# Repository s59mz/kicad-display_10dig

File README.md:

# kicad-display_10dig
A simple 10-digit 7-segment display with keyboard and PMOD interface

Schematic:
[display_10dig.pdf](display_10dig.pdf)

BOM:
[display_10dig.csv](display_10dig.csv)

Gerbers:
[gerbers.zip](https://github.com/s59mz/kicad-display_10dig/raw/main/gerbers.zip)
~

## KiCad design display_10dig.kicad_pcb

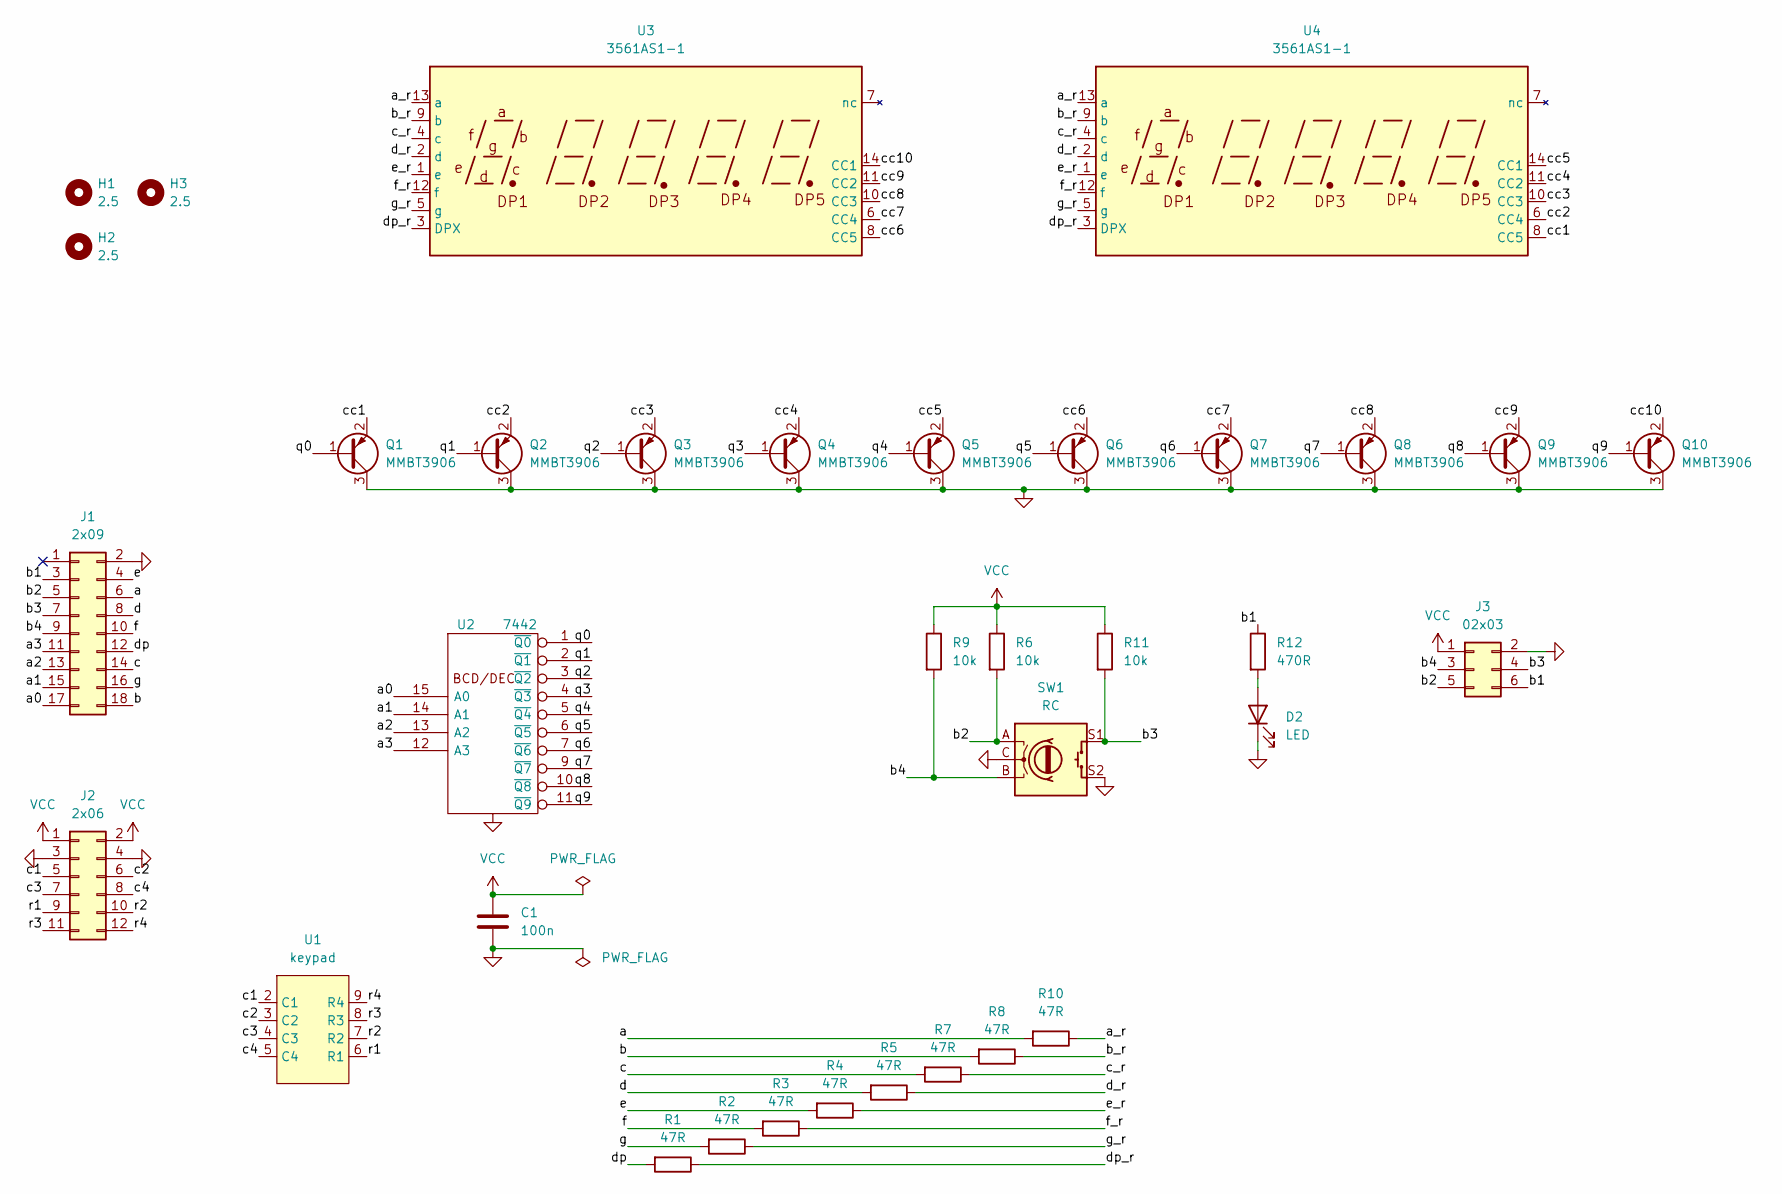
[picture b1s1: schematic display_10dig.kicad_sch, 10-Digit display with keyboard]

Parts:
C1: 100n; C_0603_1608Metric_Pad1.08x0.95mm_HandSolder
D2: LED; LED_D3.0mm
H1, H2, H3: 2.5; MountingHole_2.7mm_M2.5
J1: 2x09; PinHeader_2x09_P2.54mm_Horizontal
J2: 2x06; PinHeader_2x06_P2.54mm_Horizontal
J3: 02x03; PinHeader_2x03_P2.54mm_Vertical
Q1, Q2, Q3, Q4, Q5, Q6, Q7, Q8, Q9, Q10: MMBT3906; SOT-23
R1, R2, R3, R4, R5, R7, R8, R10: 47R; R_0603_1608Metric_Pad0.98x0.95mm_HandSolder
R6, R9, R11: 10k; R_0603_1608Metric_Pad0.98x0.95mm_HandSolder
R12: 470R; R_0603_1608Metric_Pad0.98x0.95mm_HandSolder
SW1: RC; RotaryEncoder_Alps_EC11E-Switch_Vertical_H20mm
U1: keypad; keypad hex
U2: 7442; DIP-16_W7.62mm_LongPads
U3, U4: 3561AS1-1

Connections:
/a: J1.6, R10.2
/a0: J1.17, U2.15 (A0)
/a1: J1.15, U2.14 (A1)
/a2: J1.13, U2.13 (A2)
/a3: J1.11, U2.12 (A3)
/a_r: R10.1, U3.13 (a), U4.13 (a)
/b: J1.18, R8.2
/b1: J1.3, J3.6, R12.1
/b2: J1.5, J3.5, R6.2, SW1.A
/b3: J1.7, J3.4, R11.2, SW1.S1
/b4: J1.9, J3.3, R9.2, SW1.B
/b_r: R8.1, U3.9 (b), U4.9 (b)
/c: J1.14, R7.2
/c1: J2.5, U1.2 (C1)
/c2: J2.6, U1.3 (C2)
/c3: J2.7, U1.4 (C3)
/c4: J2.8, U1.5 (C4)
/c_r: R7.1, U3.4 (c), U4.4 (c)
/cc1: Q1.2 (E), U4.8 (CC5)
/cc2: Q2.2 (E), U4.6 (CC4)
/cc3: Q3.2 (E), U4.10 (CC3)
/cc4: Q4.2 (E), U4.11 (CC2)
/cc5: Q5.2 (E), U4.14 (CC1)
/cc6: Q6.2 (E), U3.8 (CC5)
/cc7: Q7.2 (E), U3.6 (CC4)
/cc8: Q8.2 (E), U3.10 (CC3)
/cc9: Q9.2 (E), U3.11 (CC2)
/cc10: Q10.2 (E), U3.14 (CC1)
/d: J1.8, R5.2
/d_r: R5.1, U3.2 (d), U4.2 (d)
/dp: J1.12, R1.2
/dp_r: R1.1, U3.3 (DPX), U4.3 (DPX)
/e: J1.4, R4.2
/e_r: R4.1, U3.1 (e), U4.1 (e)
/f: J1.10, R3.2
/f_r: R3.1, U3.12 (f), U4.12 (f)
/g: J1.16, R2.2
/g_r: R2.1, U3.5 (g), U4.5 (g)
/q0: Q1.1 (B), U2.1 (~Q0)
/q1: Q2.1 (B), U2.2 (~Q1)
/q2: Q3.1 (B), U2.3 (~Q2)
/q3: Q4.1 (B), U2.4 (~Q3)
/q4: Q5.1 (B), U2.5 (~Q4)
/q5: Q6.1 (B), U2.6 (~Q5)
/q6: Q7.1 (B), U2.7 (~Q6)
/q7: Q8.1 (B), U2.9 (~Q7)
/q8: Q9.1 (B), U2.10 (~Q8)
/q9: Q10.1 (B), U2.11 (~Q9)
/r1: J2.9, U1.6 (R1)
/r2: J2.10, U1.7 (R2)
/r3: J2.11, U1.8 (R3)
/r4: J2.12, U1.9 (R4)
GND: C1.2, D2.1 (K), J1.2, J2.3, J2.4, J3.2, Q1.3 (C), Q2.3 (C), Q3.3 (C), Q4.3 (C), Q5.3 (C), Q6.3 (C), Q7.3 (C), Q8.3 (C), Q9.3 (C), Q10.3 (C), SW1.C, SW1.S2, U2.8 (GND)
unnamed: D2.2 (A), R12.2
VCC: C1.1, J2.1, J2.2, J3.1, R6.1, R9.1, R11.1, U2.16 (VCC)

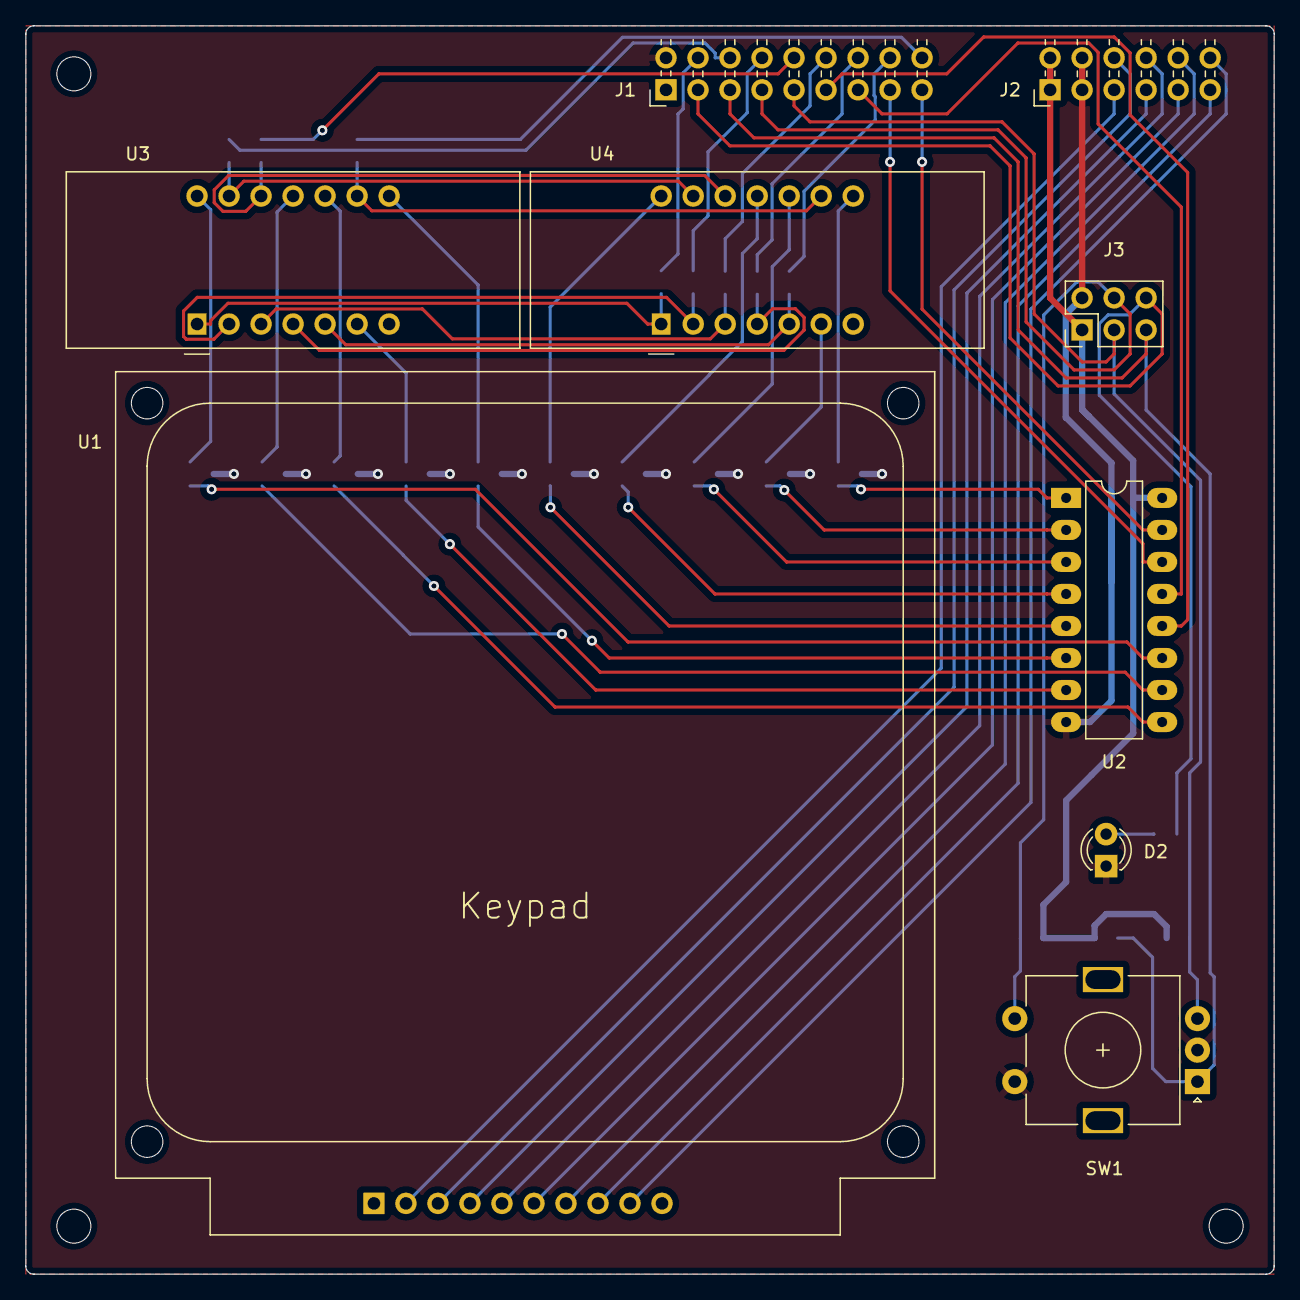
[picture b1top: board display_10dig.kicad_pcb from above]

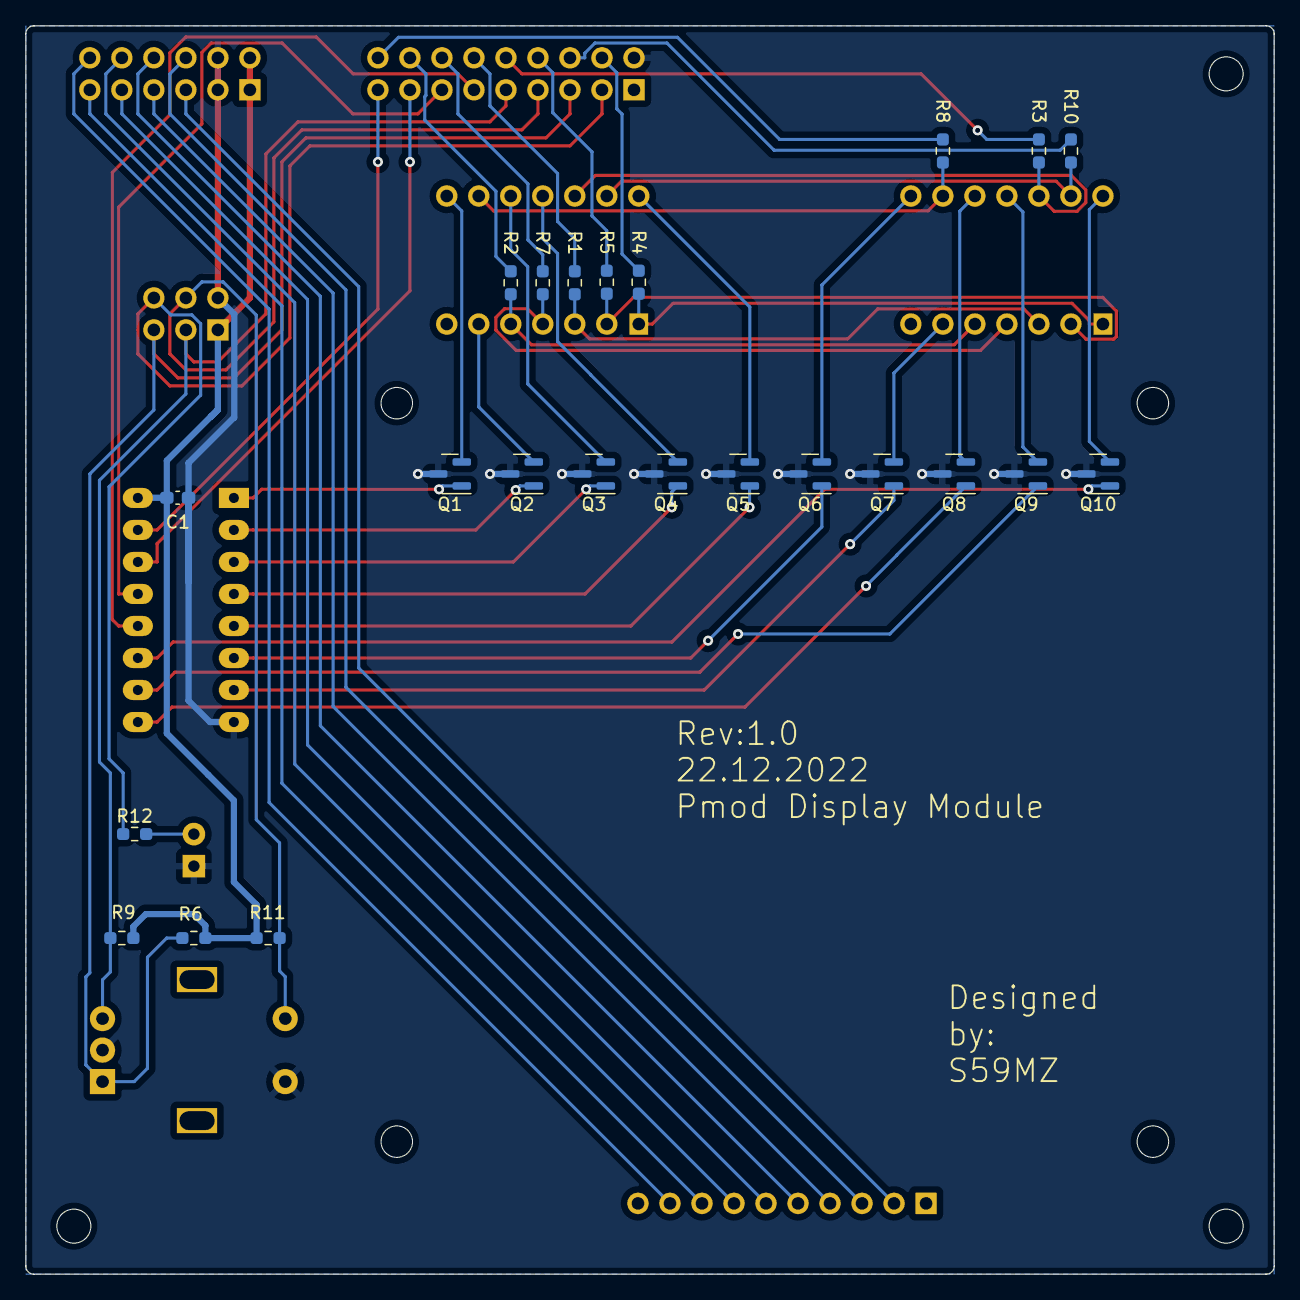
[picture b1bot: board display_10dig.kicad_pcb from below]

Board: 2 copper layers, 99.1 x 99.1 mm, 35 parts (23 on the bottom side), 55 nets.

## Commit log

2024-01-01 updated resistoor values
